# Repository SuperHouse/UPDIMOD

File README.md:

UPDI Programmer / Serial Module
===============================

Copyright 2025 SuperHouse Automation Pty Ltd  [www.superhouse.tv]()

UPDI programmer and USB-serial converter with support for automatic mode switching, 
so that a single USB connection can be used to flash, debug, and communicate with a 
target device.

This module is functionally equivalent to the excellent SerialUPDI programmer 
designed and sold by MCUdude. I'm a big fan of MCUdude's work and I've bought quite 
a few of his programmers. If you want a programmer with a USB socket that you can 
use simply by plugging it into your computer, buy his devices instead! You can get 
them here:

[www.tindie.com/products/mcudude/serialupdi-programmer/](https://www.tindie.com/products/mcudude/serialupdi-programmer/)

You should also check out MCUdude's Arduino cores that are compatible with this 
programmer, including:

 * [MegaCoreX](https://github.com/MCUdude/MegaCoreX)
 * [DxCore](https://github.com/SpenceKonde/DxCore)
 * [megaTinyCore](https://github.com/SpenceKonde/megaTinyCore)

So why does this module exist? Simply as a more convenient way to add the functionality 
of the SerialUPDI to a carrier PCB, without needing a USB cable.

Specifically, this module was designed as a building block for rapidly creating Test 
Modules for the [Testomatic PCB Test Jig System](https://github.com/superhouse/testomatic). 
It allows the tester to program and debug a target Device Under Test via UPDI, and 
communicate with it via serial UART.

However, there is nothing specific about Testomatic in this module so it can be used 
for any project that requires a UPDI programmer with serial comms.

## Features

* CH340N USB-to-serial converter
* Single-wire UPDI interface
* Selectable output voltage of 5V or 3.3V
* Switchable output power
* Serial mode, UPDI mode, or auto mode

## Pinout

The left side of the module has a 4-way header for power and USB:

* 1: 5V from host board
* 2: USB D+
* 3: USB D-
* 4: GND

The right side of the module has a 6-way header in the same format as the SerialUPDI 
programmer:

 * 1: UPDI
 * 2: VTARGET (switchable)
 * 3: RTS (not connected: can be bridged)
 * 4: TXD
 * 5: RXD
 * 6: GND

## Installation
Schematic and PCB were created in Fusion360 and provided as a Fusion360 project. They 
are also exported as EAGLE format, which can be imported back into Fusion360 or various 
other packages including KiCAD.

## Credits
Designed by Jonathan Oxer <jon@oxer.com.au>.

## Distribution
The specific terms of distribution of this project are governed by the
license referenced below.

## License
Licensed under the TAPR Open Hardware License (www.tapr.org/OHL).
The "license" folder within this repository also contains a copy of
this license in plain text format.

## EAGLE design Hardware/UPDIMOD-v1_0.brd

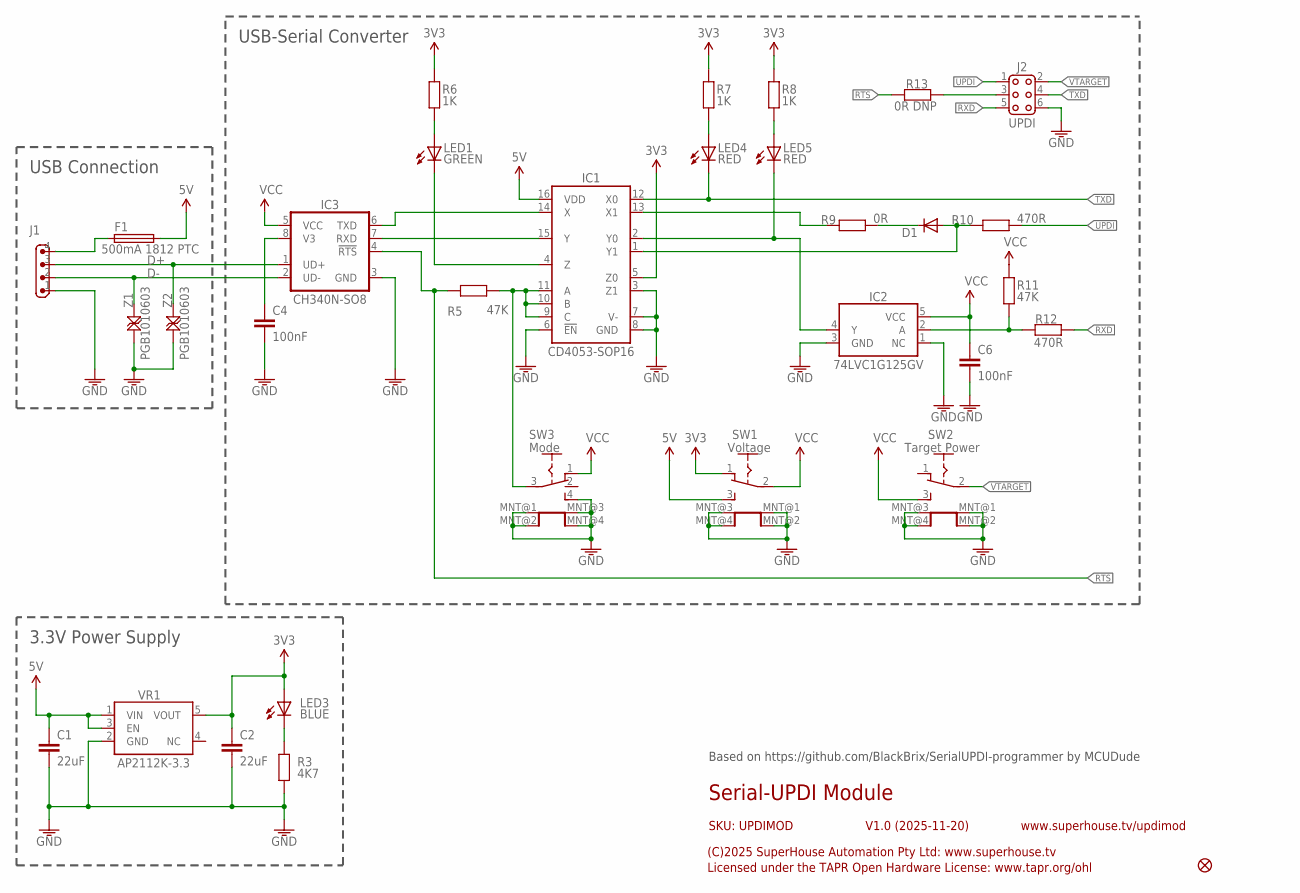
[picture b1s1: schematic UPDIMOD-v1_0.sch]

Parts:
C1, C2: 22uF; C0805
C4, C6: 100nF; C0603
D1: DIODE-SOD123; SOD-123
F1: 500mA 1812 PTC; 1206
FID2: FIDUCIAL1X2.5; FIDUCIAL-1X2.5
IC1: CD4053-SOP16; SO16
IC2: 74LVC1G125GV; SOT23-5
IC3: CH340N-SO8; SOIC8
J1: M04-PIN-BELOW; 1X04-P-BELOW
J2: UPDI; 2X03-S-BELOW
LED1: GREEN; LED-0603
LED3: BLUE; LED-0603
LED4, LED5: RED; LED-0603
R3: 4K7; R0603
R5, R11: 47K; R0603
R6, R7, R8: 1K; R0603
R9: 0R; R0603
R10, R12: 470R; R0603
R13: 0R DNP; R0603
SW1: Voltage; MK-12C02
SW2: Target Power; MK-12C02
SW3: Mode; MK-13C02
VR1: AP2112K-3.3; SOT23-5
Z1, Z2: PGB1010603; TVS0603

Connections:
3.3V: C2.1, IC1.5 (Z0), LED3.A, R6.2, R7.2, R8.2, SW1.1 (A), VR1.5 (VOUT)
5V: C1.1, F1.2, IC1.16 (VDD), SW1.3 (B), VR1.1 (VIN), VR1.3 (EN)
D+: IC3.1 (UD+), J1.3, Z2.2
D-: IC3.2 (UD-), J1.2, Z1.2
GND: C1.2, C2.2, C4.2, C6.2, IC1.3 (Z1), IC1.6 (!EN), IC1.7 (V-), IC1.8 (GND), IC2.1 (NC), IC2.3 (GND), IC3.3 (GND), J1.1, J2.6, R3.1, SW1.MNT@1 (MNT), SW1.MNT@2 (MNT), SW1.MNT@3 (MNT), SW1.MNT@4 (MNT), SW2.MNT@1 (MNT), SW2.MNT@2 (MNT), SW2.MNT@3 (MNT), SW2.MNT@4 (MNT), SW3.4 (C), SW3.MNT@1 (MNT), SW3.MNT@2 (MNT), SW3.MNT@3 (MNT), SW3.MNT@4 (MNT), VR1.2 (GND), Z1.1, Z2.1
unnamed: C4.1, IC3.8 (V3)
unnamed: LED1.A, R6.1
unnamed: IC1.4 (Z), LED1.C
unnamed: LED3.C, R3.2
unnamed: IC1.14 (X), IC3.6 (TXD)
unnamed: IC1.15 (Y), IC3.7 (RXD)
unnamed: LED5.A, R8.1
unnamed: IC1.9 (C), IC1.10 (B), IC1.11 (A), R5.1, SW3.3 (COM)
unnamed: LED4.A, R7.1
unnamed: IC1.13 (X1), R9.2
unnamed: IC1.2 (Y0), IC2.4 (Y), LED5.C
unnamed: D1.1 (C), R9.1
unnamed: D1.2 (A), IC1.1 (Y1), R10.2
unnamed: IC2.2 (A), R11.1, R12.2
unnamed: J2.3, R13.1
RTS: IC3.4 (!RTS), R5.2, R13.2
RXD: J2.5, R12.1
TXD: IC1.12 (X0), J2.4, LED4.C
UPDI: J2.1, R10.1
VCC: C6.1, IC2.5 (VCC), IC3.5 (VCC), R11.2, SW1.2 (COM), SW2.3 (B), SW3.1 (A)
VIN: F1.1, J1.4
VTARGET: J2.2, SW2.2 (COM)

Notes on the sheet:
Serial-UPDI Module
V1.0 (2025-11-20)
SKU: UPDIMOD
(C)2025 SuperHouse Automation Pty Ltd: www.superhouse.tv
Licensed under the TAPR Open Hardware License: www.tapr.org/ohl
www.superhouse.tv/updimod
USB Connection
USB-Serial Converter
3.3V Power Supply
Based on https://github.com/BlackBrix/SerialUPDI-programmer by MCUDude

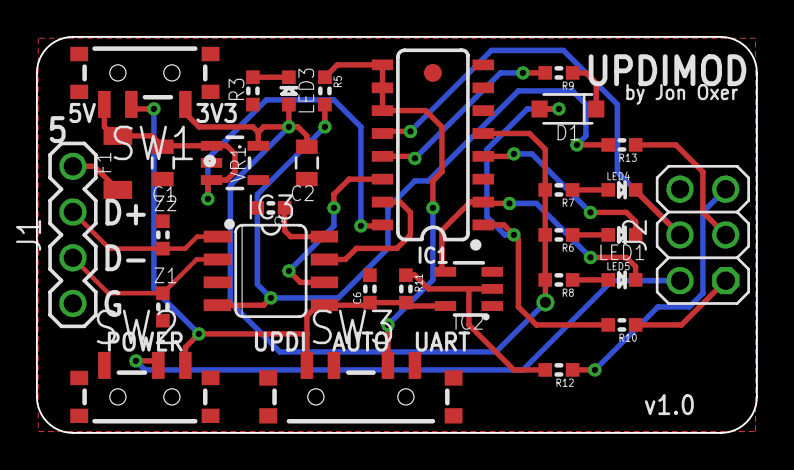
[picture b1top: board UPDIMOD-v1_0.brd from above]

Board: 2 copper layers, 40.0 x 22.0 mm, 32 parts (0 on the bottom side), 27 nets.

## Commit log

2025-12-05 Initialised repo
2025-12-05 Initial import of project files.
2025-12-05 Added PDF of schematic for convenience
